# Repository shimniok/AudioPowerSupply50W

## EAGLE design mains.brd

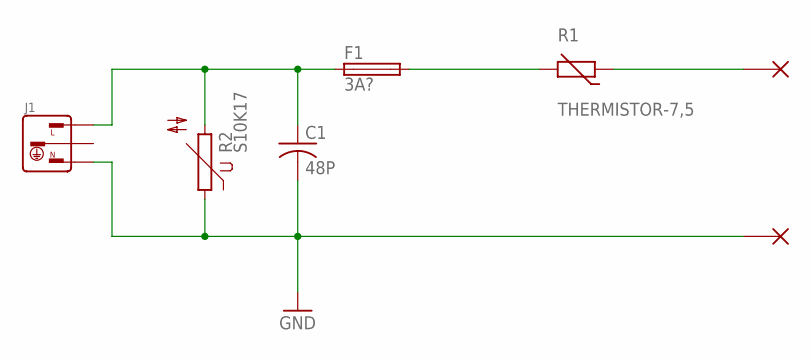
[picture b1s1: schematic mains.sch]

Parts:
C1: 48P; C075
F1: 3A?; FUSE_HOLDER_5X20MM
J1: AC-JACK-3-ADAMTEC-IEC-A-4; ADAMTEC-IEC-A-4
R1: THERMISTOR-7,5; R-7,5
R2: S10K17
X3, X4: WIREPAD_14GA; PAD_14GA

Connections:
GND: C1.2 (-), J1.N, R2.1, X4.P$1
unnamed: C1.1 (+), F1.1, J1.L, R2.2
unnamed: F1.2, R1.2
unnamed: R1.1, X3.P$1

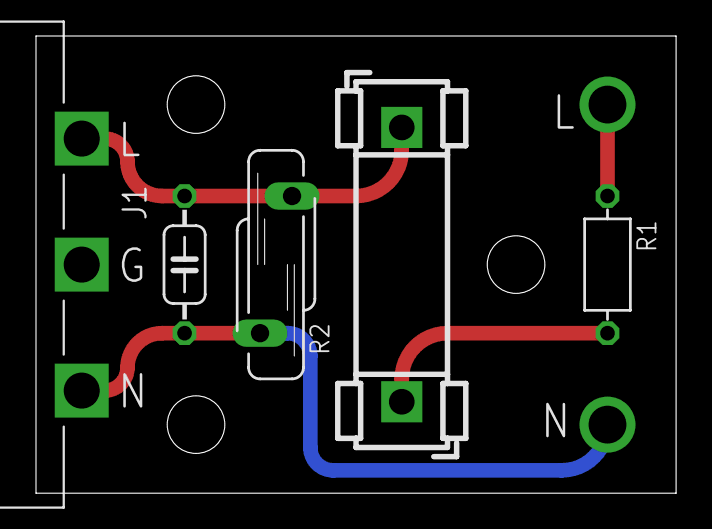
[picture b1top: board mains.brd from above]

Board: 2 copper layers, 35.6 x 25.4 mm, 7 parts (0 on the bottom side), 4 nets.

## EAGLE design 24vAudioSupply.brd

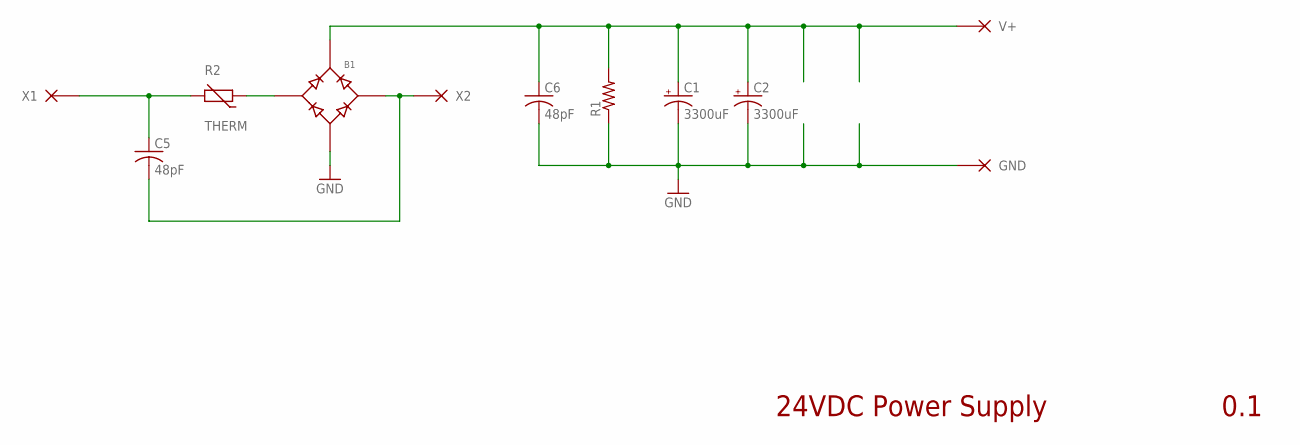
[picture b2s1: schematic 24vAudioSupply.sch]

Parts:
B1: RECTIFIER-GBPC-W; GBPC-W
C1, C2: 3300uF; E7,5-18
C5, C6: 48pF; C075
R1: R0204/7-PTH; 0204/7
R2: THERM; R-7,5
X1: X1; PAD_14GA
X2: X2; PAD_14GA
X3: V+; PAD_12GA
X4: GND; PAD_12GA

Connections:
GND: B1.V- (-), C1.-, C2.-, C6.2 (-), R1.1, X4.P$1
unnamed: C5.1 (+), R2.2, X1.P$1
V+: B1.V+ (+), C1.+, C2.+, C6.1 (+), R1.2, X3.P$1
X1: B1.AC1, R2.1
X2: B1.AC2, C5.2 (-), X2.P$1

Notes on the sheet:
24VDC Power Supply
0.1

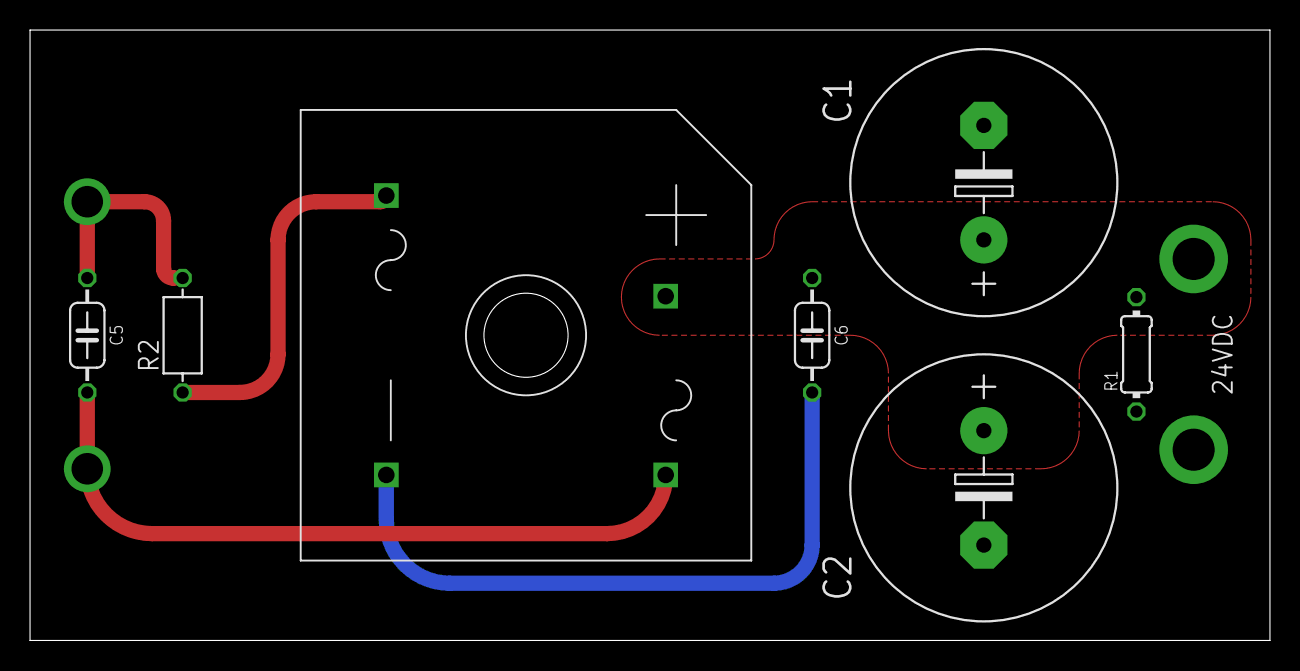
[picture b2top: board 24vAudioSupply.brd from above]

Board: 2 copper layers, 82.5 x 40.6 mm, 11 parts (0 on the bottom side), 5 nets.

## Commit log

2023-08-28 initial version
2023-08-29 convert raw adc values to amps, per acs714 datasheet
2023-08-29 datasheets
2023-08-29 spice sim files
2023-08-29 captured inrush current data
